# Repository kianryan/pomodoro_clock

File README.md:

## Introduction

Pomodoro Clock for AtTiny84 and MAX7219.

## Prerequisites

Arduino Cli

```
choco install arduino-cli
```

Install ATTinyCore Core

```
arduino-cli core install ATTinyCore:avr
```

## Building

* Arduino CLI
* USBAsp

Compiles, generates build asset in /build and uploads via ASP.

```
arduino-cli compile --fqbn ATTinyCore:avr:attinyx4; arduino-cli upload --fqbn ATTinyCore:avr:attinyx4 -P usbasp
```

## Board and Schematics

Eagle designs are available in /eagle

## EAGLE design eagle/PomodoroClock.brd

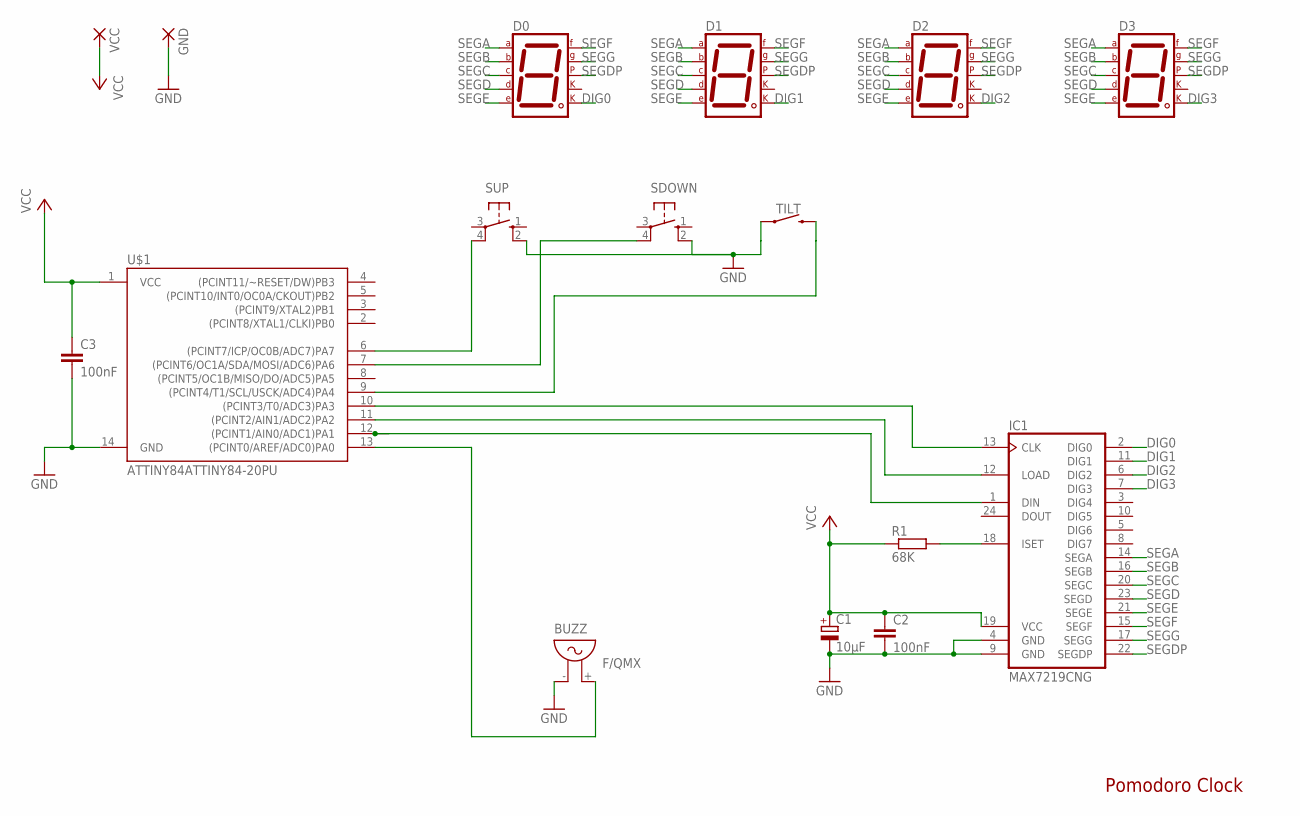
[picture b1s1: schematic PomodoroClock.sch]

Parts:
BUZZ: F/QMX
C1: 10μF; E2,5-6E
C2, C3: 100nF; C025-025X050
D0, D1, D2, D3: 7SEG-CK; 7SEG-13
GND: 3,81/1,4
IC1: MAX7219CNG; DIL24-3
R1: 68K; 0207/10
SDOWN: 10-XX; B3F-10XX
SUP: 10-XX; B3F-10XX
TILT: TILT
U$1: ATTINY84ATTINY84-20PU; DIP14
VCC: 3,81/1,4

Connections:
DIG0: D0.8 (CK2), IC1.2 (DIG0)
DIG1: D1.8 (CK2), IC1.11 (DIG1)
DIG2: D2.8 (CK2), IC1.6 (DIG2)
DIG3: D3.8 (CK2), IC1.7 (DIG3)
GND: BUZZ.- (1), C1.-, C2.2, C3.2, GND.1, IC1.4 (GND), IC1.9 (GND), SDOWN.2 (S1), SUP.2 (S1), TILT.1 (3), U$1.14 (GND)
unnamed: IC1.13 (CLK), U$1.10 ((PCINT3/T0/ADC3)PA3)
unnamed: IC1.12 (LOAD), U$1.11 ((PCINT2/AIN1/ADC2)PA2)
unnamed: IC1.1 (DIN), U$1.12 ((PCINT1/AIN0/ADC1)PA1)
unnamed: BUZZ.+ (2), U$1.13 ((PCINT0/AREF/ADC0)PA0)
unnamed: SUP.4 (P1), U$1.6 ((PCINT7/ICP/OC0B/ADC7)PA7)
unnamed: SDOWN.4 (P1), U$1.7 ((PCINT6/OC1A/SDA/MOSI/ADC6)PA6)
unnamed: IC1.18 (ISET), R1.2
SEGA: D0.7 (A), D1.7 (A), D2.7 (A), D3.7 (A), IC1.14 (SEGA)
SEGB: D0.6 (B), D1.6 (B), D2.6 (B), D3.6 (B), IC1.16 (SEGB)
SEGC: D0.4 (C), D1.4 (C), D2.4 (C), D3.4 (C), IC1.20 (SEGC)
SEGD: D0.2 (D), D1.2 (D), D2.2 (D), D3.2 (D), IC1.23 (SEGD)
SEGDP: D0.5 (DP), D1.5 (DP), D2.5 (DP), D3.5 (DP), IC1.22 (SEGDP)
SEGE: D0.1 (E), D1.1 (E), D2.1 (E), D3.1 (E), IC1.21 (SEGE)
SEGF: D0.9 (F), D1.9 (F), D2.9 (F), D3.9 (F), IC1.15 (SEGF)
SEGG: D0.10 (G), D1.10 (G), D2.10 (G), D3.10 (G), IC1.17 (SEGG)
TILT: TILT.2 (4), U$1.9 ((PCINT4/T1/SCL/USCK/ADC4)PA4)
VCC: C1.+, C2.1, C3.1, IC1.19 (VCC), R1.1, U$1.1 (VCC), VCC.1

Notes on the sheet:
Pomodoro Clock

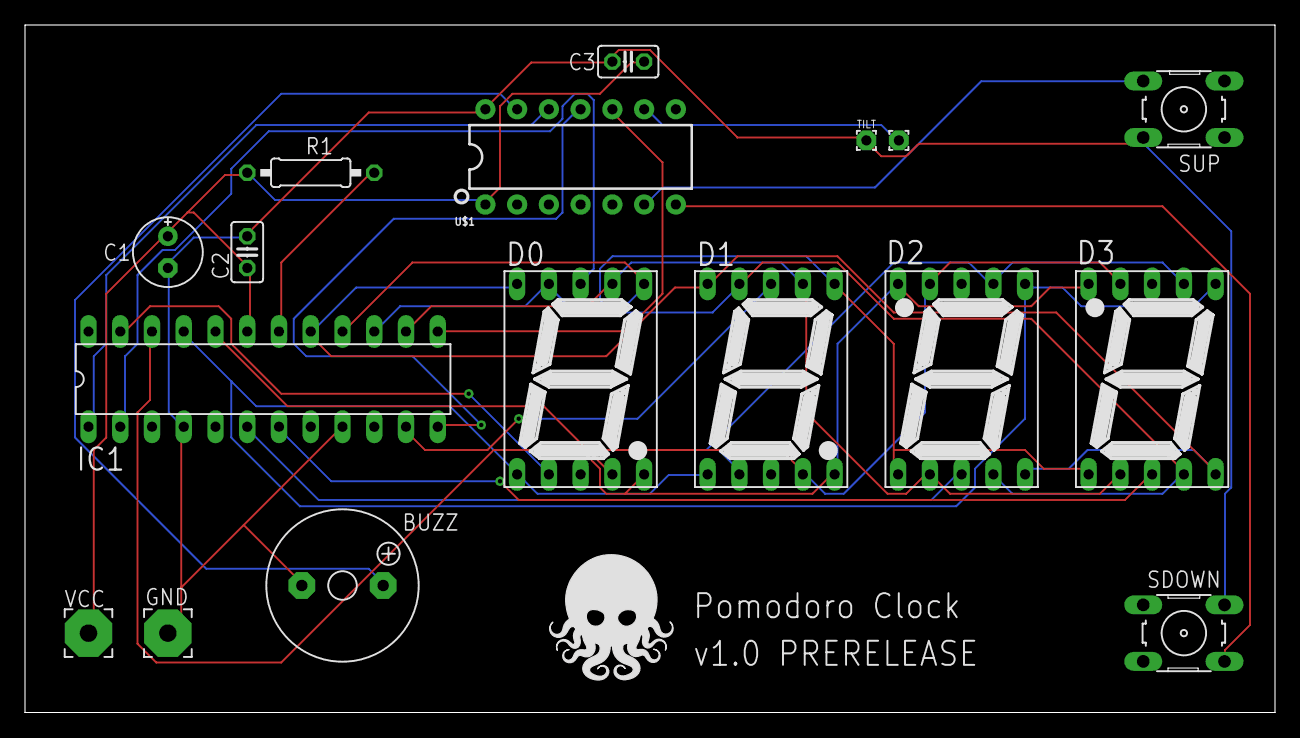
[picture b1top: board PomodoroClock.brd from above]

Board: 2 copper layers, 100.0 x 55.0 mm, 16 parts (0 on the bottom side), 22 nets.

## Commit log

2020-03-22 Detect when tilt changes and reset timer.
2020-03-22 Update resettimer for the given clock
2020-03-22 Add easing button, accl change state.
2020-03-22 Add a decreasing button.
2020-03-28 Change PomoTimer to track elapsed time over DateTime
2020-03-29 Build a button manager to handle button states
2020-03-29 Change ctor method for EasingButton
2020-03-29 Change ctor for TiltSwitch, remember to actually read tilt.
2020-03-29 Add UI manager to take over handling display
2020-03-29 Add pre-flight to allow periods to be adjusted
2020-03-29 Sound alarm on completion
2020-04-10 Switch RTC clock to use internal Mills
2020-04-10 Inverse digits
2020-04-13 Replace ADAFruit RTCClock with MilliClock
    RTCClock can only count in seconds - use MilliClock which can count in milliseconds.
2020-04-13 Update EasingButton
2020-04-13 Pause timer on pre-flight
2020-04-20 Boundary conditions for setting timers
2020-04-20 Store timer values in EEPROM. Read/write before flight
2020-04-20 Comment out superflous serial lines
2020-04-20 Inverse buttons based on direction
2020-04-20 Add piezo alarm back in. :-(
2020-04-20 Add "bump" in timer when at zero, remove serial
2020-09-27 Add ignore for arduino cli build
2020-09-27 TiltSwitch now returns bool
2020-09-27 UiManager now uses straight digit wiring...
    I meant to do that.
2020-09-27 Debug direction and display
2020-09-27 Add readme
2020-12-10 Add eagle designs

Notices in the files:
parts and their libraries:
SparkFun-IC-Microcontroller: Licensing: Creative Commons ShareAlike 4.0 International - https://creativecommons.org/licenses/by-sa/4.0
